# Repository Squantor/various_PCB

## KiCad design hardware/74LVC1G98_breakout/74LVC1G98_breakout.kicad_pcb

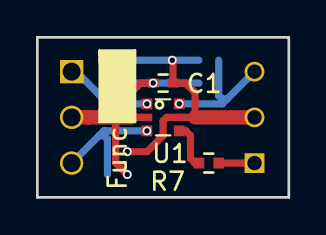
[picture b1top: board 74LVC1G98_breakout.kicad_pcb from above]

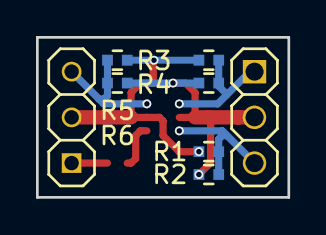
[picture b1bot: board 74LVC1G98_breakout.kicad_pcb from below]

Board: 2 copper layers, 14.0 x 8.9 mm, 12 parts (8 on the bottom side), 7 nets.

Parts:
C1: 100n; C_0402
J1: PINS_1X03; Header-0254-1X03-H010
J2: PINS_1X03; Header-0254-1X03-H008
L1: Func; Label_Note_small
R1, R2, R3, R4, R5, R6: 10k; R_0402_hand
R7: R; R_0402_hand
U1: 74LVC1G98; SOT363

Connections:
A: J1.3, R1.2, R2.1, U1.3
B: J1.1, R3.2, R4.1, U1.1
C: J2.3, R5.2, R6.1, U1.6
GND: C1.2, J1.2, R2.2, R4.2, R6.2, U1.2
unnamed: J2.1, R7.1
VCC: C1.1, J2.2, R1.1, R3.1, R5.1, U1.5
Y: R7.2, U1.4

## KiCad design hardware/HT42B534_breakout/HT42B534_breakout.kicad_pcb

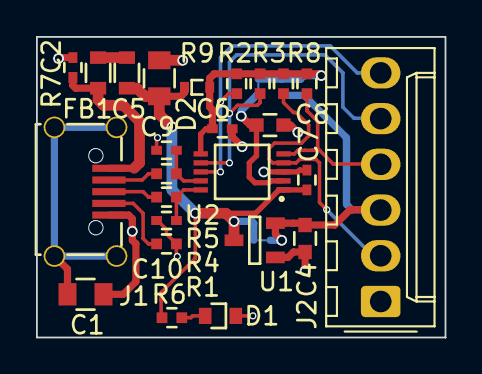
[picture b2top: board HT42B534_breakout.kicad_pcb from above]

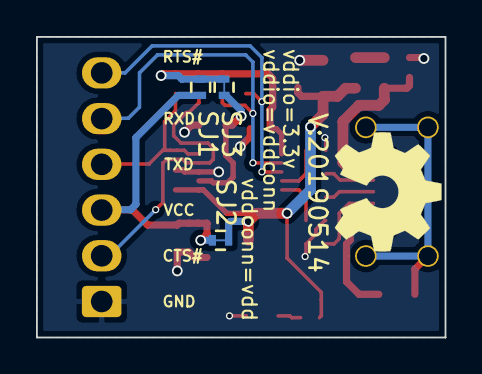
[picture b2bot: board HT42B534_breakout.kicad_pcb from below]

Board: 2 copper layers, 22.7 x 16.7 mm, 30 parts (5 on the bottom side), 18 nets.

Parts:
C1: 100n; C_0805
C2, C6, C7: 100n; C_0402
C4, C8: 1u; C_0603
C5: 10u; C_0805
C9, C10: 47p; C_0402
D1: RED; D_0603_hand
D2: D_Schottky; SOD-523
FB1: 600; R_0603_hand
J1: USB-ID; USB-muB-SMD_TH
J2: FTDI_PINS_1X06_input; Molex_KK-254_AE-6410-06A_1x06_P2.54mm_Vertical_FTDI_UART
N1: OHWLOGO; OSHW-Symbol_6.7x6mm_SilkScreen
N2: 20190514; Label_version
R1: 0; R_0402_hand
R2, R3, R8, R9: 10K; R_0402_hand
R4, R5: 33; R_0402_hand
R6: 1K; R_0402_hand
R7: Fuse; R_0603_hand
SJ1: vddio=vddconn; solder_jumper_2way_noconn
SJ2: vddconn=vdd; solder_jumper_2way_conn
SJ3: vddio=3.3v; solder_jumper_2way_conn
U1: MCP1702-CB; SOT23-3-Microchip-TT
U2: HT42B534-MSOP10; MSOP-10

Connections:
/CTSI: J2.2, R3.1, U2.4
/RTSO: J2.6, R9.1, U2.8
/RXI: J2.5, R2.1, U2.7
/TXO: J2.4, R8.1, U2.5
/USB_DM: J1.2, R5.1
/USB_DP: J1.3, R4.1
/VBUS: C2.1, J1.1, R7.2
/VDD: C5.1, C7.1, D2.1, FB1.1, R6.2, SJ2.2, U1.3, U2.1
/VDDCONN: C4.1, J2.3, SJ1.1, SJ2.1, U1.2
/VDDIO: C6.1, D2.2, R2.2, R3.2, R8.2, R9.2, SJ1.2, SJ3.1, U2.6
/VDD_33V: C8.1, SJ3.2, U2.2
/VSS: C1.2, C2.2, C4.2, C5.2, C6.2, C7.2, C8.2, C9.1, C10.1, D1.1, J1.5, J2.1, R1.2, U1.1, U2.3
unnamed: C1.1, J1.S
unnamed: C9.2, R5.2, U2.9
unnamed: C10.2, R4.2, U2.10
unnamed: D1.2, R6.1
unnamed: FB1.2, R7.1
unnamed: J1.4, R1.1

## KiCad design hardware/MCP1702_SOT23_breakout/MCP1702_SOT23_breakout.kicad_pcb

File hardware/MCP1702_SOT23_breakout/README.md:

# MCP1702 SOT23 breakout
Simple breakout for the SOT23 packaged MCP1702
## TODO's
Still some things need to be done:
* Produce at [OSHPARK](https://oshpark.com/) (WIP)
* Assemble (TODO)
* Test & characterise (TODO)
* update Readme.md with pictures and BOM (TODO)
## BOM
Due to the general shortage of passive components, where mentioned, just whatever you can find.
* [MCP1702](http://ww1.microchip.com/downloads/en/DeviceDoc/22008E.pdf)
Dual 0805/0603 footprint present to accomodate a few capacitor types.

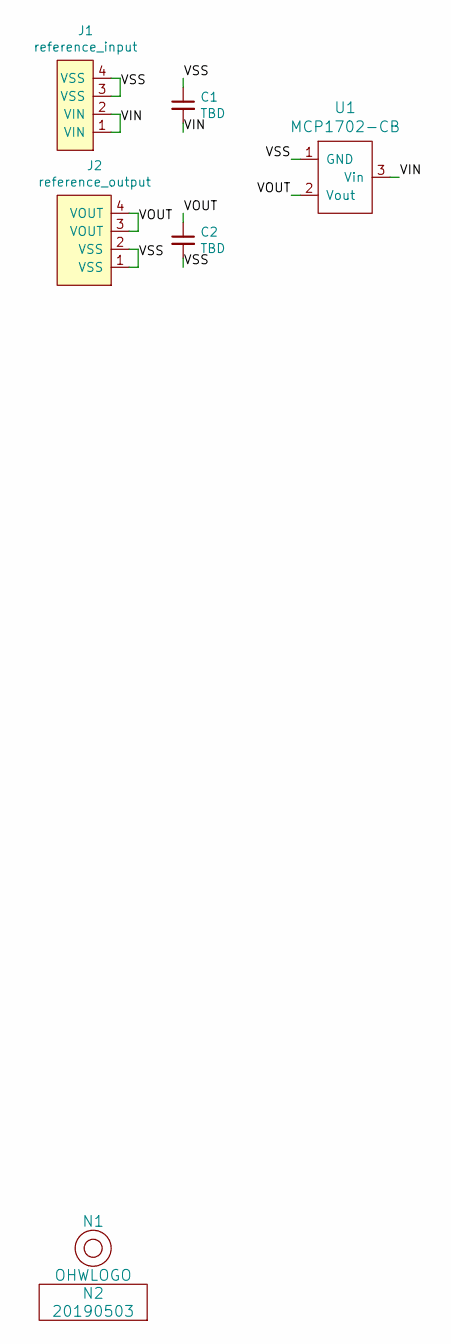
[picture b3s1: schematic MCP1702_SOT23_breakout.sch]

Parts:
C1, C2: TBD; C_0805+0603
J1: reference_input
J2: reference_output
N1: OHWLOGO; OSHW-Symbol_6.7x6mm_SilkScreen
N2: 20190503; Label_version
U1: MCP1702-CB; SOT23-3-Microchip-CB

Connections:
/VIN: C1.2, J1.1 (VIN), J1.2 (VIN), U1.3 (Vin)
/VOUT: C2.1, J2.3 (VOUT), J2.4 (VOUT), U1.2 (Vout)
/VSS: C1.1, C2.2, J1.3 (VSS), J1.4 (VSS), J2.1 (VSS), J2.2 (VSS), U1.1 (GND)

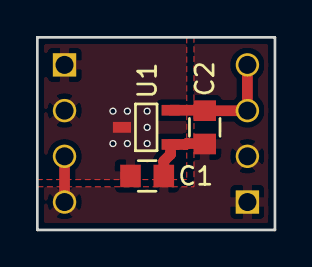
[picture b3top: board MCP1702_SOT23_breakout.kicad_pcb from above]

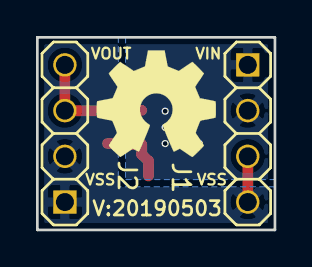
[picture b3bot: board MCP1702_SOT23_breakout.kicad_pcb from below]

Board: 2 copper layers, 13.2 x 10.7 mm, 7 parts (3 on the bottom side), 3 nets.

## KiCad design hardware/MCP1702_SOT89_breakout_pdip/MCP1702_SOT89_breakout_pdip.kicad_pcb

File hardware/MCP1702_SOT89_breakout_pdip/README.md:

# MCP1702 PDIP adapter
Very simple PDIP adapter for the MCP1702 LDO
## TODO's
Still some things need to be done:
* schematic entry (Done)
* PCB layout (Done)
* Review with one night in between (Done)
* Produce at [OSHPARK](https://oshpark.com/) (In progress)
* Assemble (TODO)
* Test & characterise (TODO)
* update Readme.md with pictures and BOM (TODO)
## BOM
## Pictures

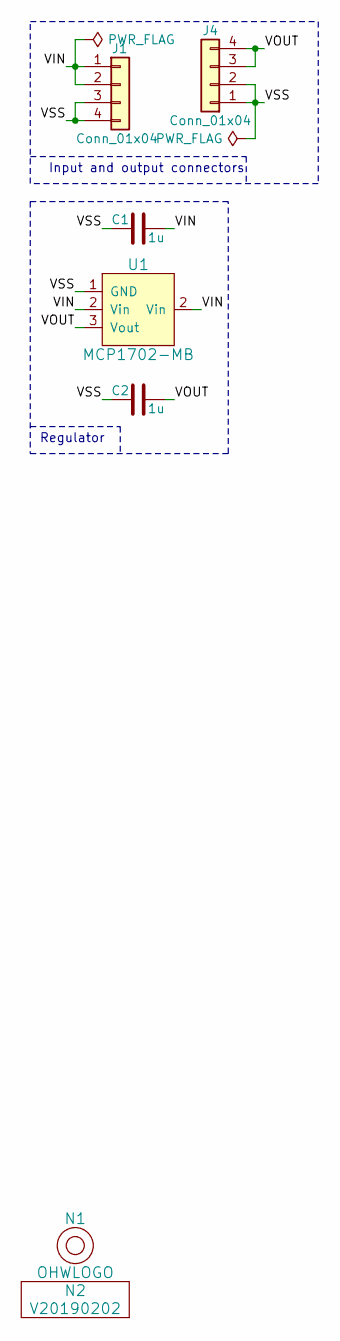
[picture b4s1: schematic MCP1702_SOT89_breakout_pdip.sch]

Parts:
C1, C2: 1u; C_0805
J1, J4: Conn_01x04; PinHeader_1x04_P2.54mm_Vertical
N1: OHWLOGO; OSHW-Symbol_6.7x6mm_SilkScreen
N2: V20190202; Label_Generic
U1: MCP1702-MB; SOT89-NXP

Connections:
/VIN: C1.1, J1.1, J1.2, U1.2 (Vin)
/VOUT: C2.1, J4.3, J4.4, U1.3 (Vout)
/VSS: C1.2, C2.2, J1.3, J1.4, J4.1, J4.2, U1.1 (GND)

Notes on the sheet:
Input and output connectors
Regulator

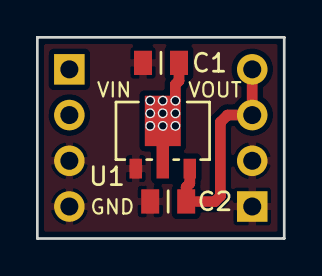
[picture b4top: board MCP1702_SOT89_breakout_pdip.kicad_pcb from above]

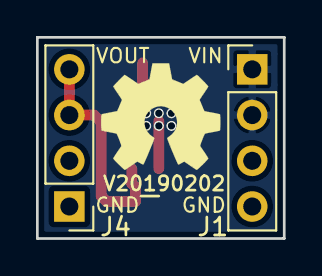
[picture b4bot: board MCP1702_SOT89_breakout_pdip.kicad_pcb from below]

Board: 2 copper layers, 13.7 x 11.2 mm, 7 parts (4 on the bottom side), 3 nets.

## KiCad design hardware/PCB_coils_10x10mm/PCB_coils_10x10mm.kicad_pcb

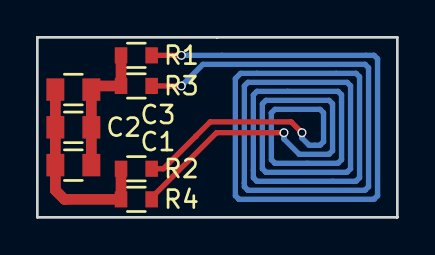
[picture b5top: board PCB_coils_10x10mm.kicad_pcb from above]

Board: 2 copper layers, 20.0 x 10.0 mm, 7 parts (0 on the bottom side), 4 nets.

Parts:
C1, C2, C3: C; C_0805
R1, R2, R3, R4: 0; R_0603_hand

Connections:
/COIL1: R1.1, R2.1
/COIL2: R3.1, R4.1
unnamed: C1.1, C2.1, C3.1, R2.2, R4.2
unnamed: C1.2, C2.2, C3.2, R1.2, R3.2

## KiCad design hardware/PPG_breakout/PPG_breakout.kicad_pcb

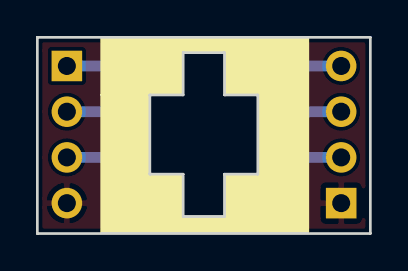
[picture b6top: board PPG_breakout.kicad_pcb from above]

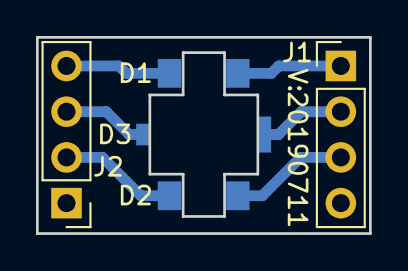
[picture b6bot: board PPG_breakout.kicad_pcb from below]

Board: 2 copper layers, 18.5 x 10.9 mm, 6 parts (6 on the bottom side), 7 nets.

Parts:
D1, D2: LED; KPTR-3216
D3: D_Photo; SFH2440_reverse
J1, J2: Conn_01x04; PinHeader_1x04_P2.54mm_Vertical
N2: 20190711; Label_version

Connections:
/LED1_A: D1.2, J1.1
/LED1_C: D1.1, J2.4
/LED2_A: D2.2, J1.3
/LED2_C: D2.1, J2.2
/PD_A: D3.2, J1.2
/PD_C: D3.1, J2.3
/VSS: J1.4, J2.1

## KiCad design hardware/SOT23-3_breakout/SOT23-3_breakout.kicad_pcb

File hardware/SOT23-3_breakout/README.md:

# SOT23 3 pin breakout
Simple SOT23 3 pin breakout. Ideal for breadboarding small mosfets and such.
## TODO's
Still some things need to be done:
* schematic entry (Done)
* PCB layout (Done)
* Review with one night in between (TODO)
* Produce at [OSHPARK](https://oshpark.com/) (TODO)
* Assemble (TODO)

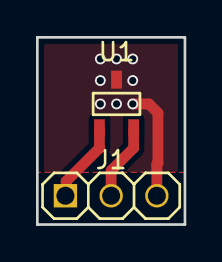
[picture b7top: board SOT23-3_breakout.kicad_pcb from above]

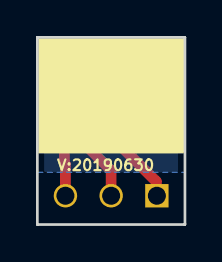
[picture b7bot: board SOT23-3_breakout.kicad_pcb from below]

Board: 2 copper layers, 8.2 x 10.4 mm, 4 parts (2 on the bottom side), 3 nets.

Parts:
J1: PINS_1X03; Header-0254-1X03-H010
N1: OHWLOGO; OSHW-Symbol_6.7x6mm_SilkScreen
N2: 20190630; Label_version
U1: Generic_SOT23-3; SOT23-3-Microchip-CB

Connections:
/PIN_1: J1.1, U1.1
/PIN_2: J1.2, U1.2
/PIN_3: J1.3, U1.3
